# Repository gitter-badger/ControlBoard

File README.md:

ControlBoard
============

HAAG Control Board Schematics and Board Design

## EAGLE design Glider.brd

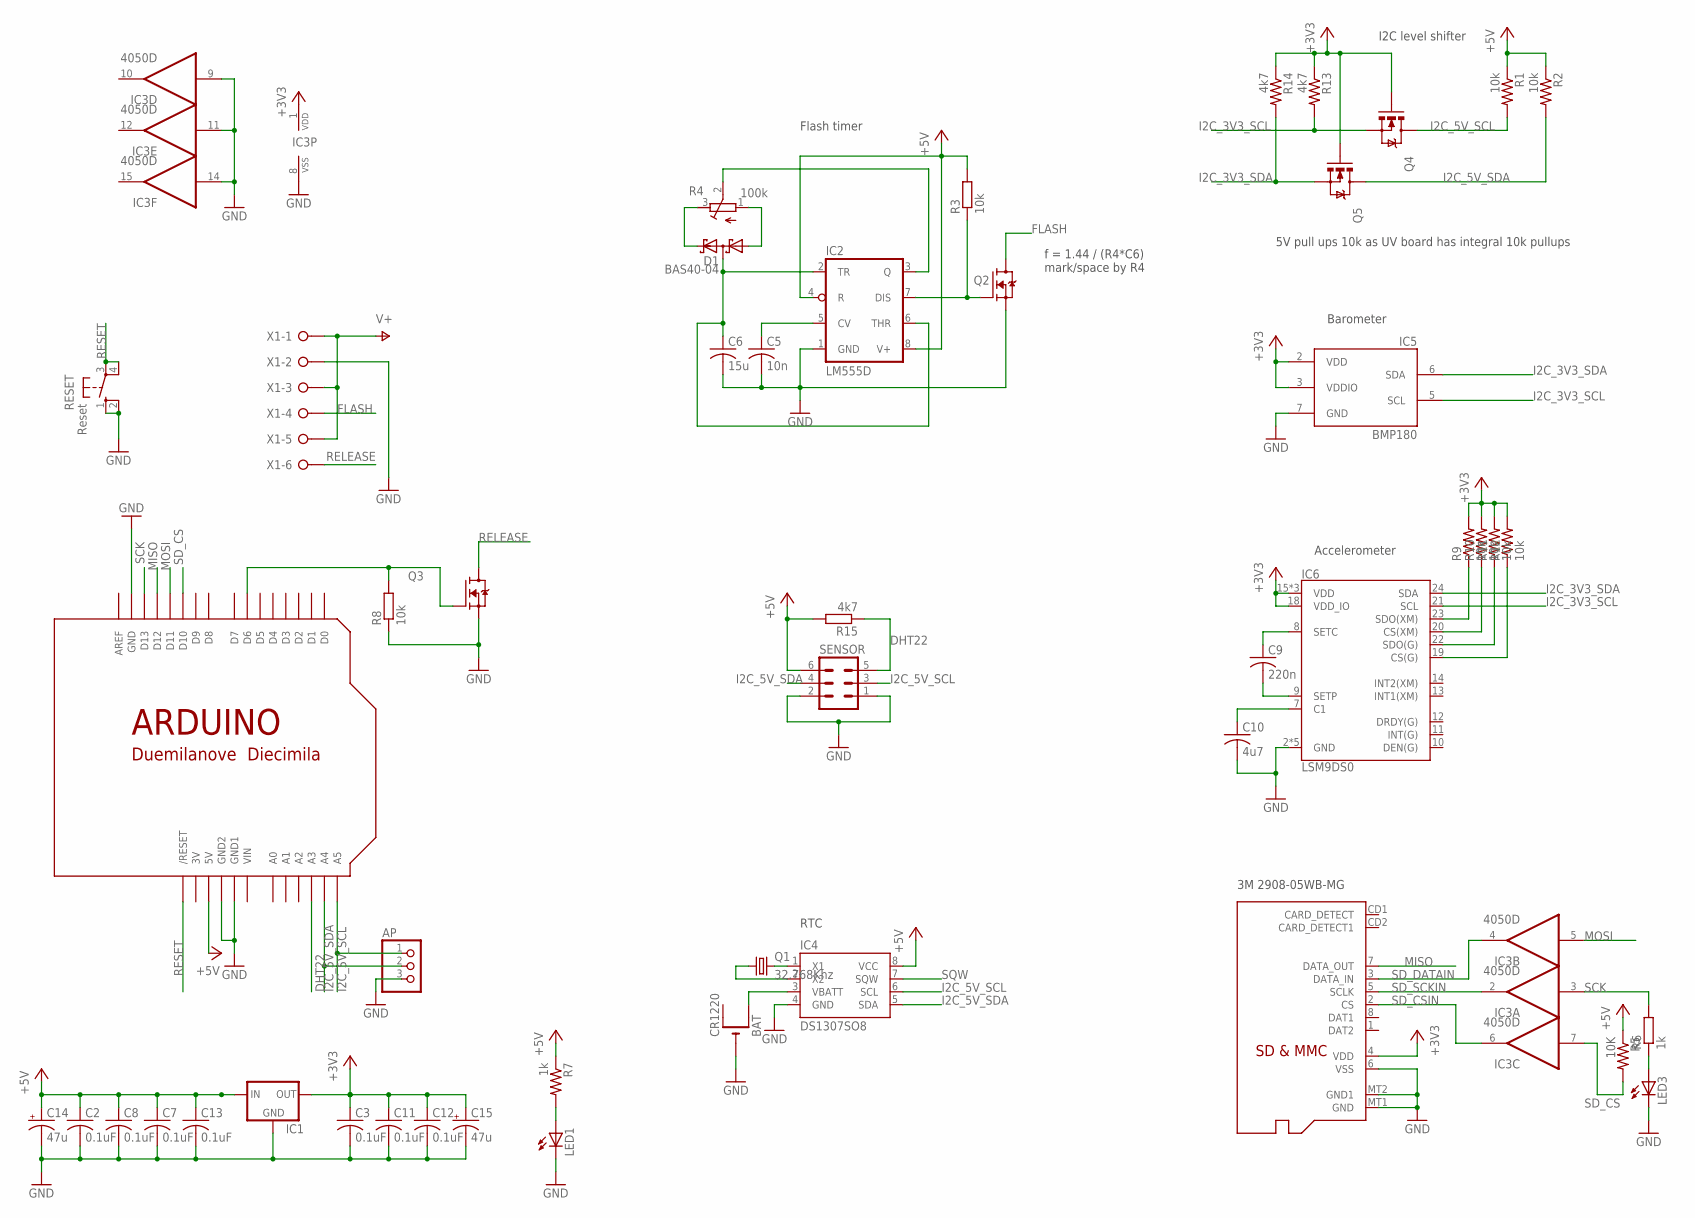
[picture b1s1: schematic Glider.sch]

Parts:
AP: PINHD-1X3; 1X03
BAT: CR1220; CR1220-THM
C2, C3, C7, C8, C11, C12, C13: 0.1uF; C0805
C5: 10n; C0805
C6: 15u; C0805
C9: 220n; C0603
C10: 4u7; C0603
C14, C15: 47u; SMC_B
D1: BAS40-04; SOT23
IC1: MCP1700TT; SOT-23
IC2: LM555D; SO08
IC3: 4050D; SO16
IC4: DS1307SO8; SO08
IC5: BMP180
IC6: LSM9DS0; LGA-24
LED1, LED3: LEDCHIPLED_0805; CHIPLED_0805
Q1: 32.768Khz; TC38H
Q2, Q3: NTD20N06LT4G; TO252
Q4, Q5: MOSFET-NCHANNELBSS123LT1G; SOT23-3
R1, R2, R3, R8, R9, R10, R11, R12: 10k; R0805
R4: 100k; RTRIM3214W
R5: 10K; R0805
R6, R7: 1k; R0805
R13, R14, R15: 4k7; R0805
RESET: Reset; B3F-10XX
SD: MICROSD
SENSOR: ML6
U$1: ARDUINODUEMILANOVE-NOHOLES; ARDUINO-NOHOLE
X1: W237-06P; W237-6P

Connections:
3V: U$1.3V
+3V3: C3.1, C11.1, C12.1, C15.+, IC1.2 (OUT), IC3.1 (VDD), IC5.2 (VDD), IC5.3 (VDDIO), IC6.15 (VDD), IC6.16 (VDD), IC6.17 (VDD), IC6.18 (VDD_IO), Q4.1 (G), Q5.1 (G), R9.2, R10.2, R11.2, R12.2, R13.1, R14.1, SD.4 (VDD)
+5V: C2.1, C7.1, C8.1, C13.1, C14.+, IC1.3 (IN), IC2.4 (R), IC2.8 (V+), IC4.8 (VCC), R1.1, R2.1, R3.2, R5.1, R7.1, R15.2, SENSOR.6, U$1.5V
DHT22: R15.1, SENSOR.5, U$1.A3
FLASH: Q2.4 (D), X1.4
GND: AP.3, BAT.-, C2.2, C3.2, C5.2, C6.2, C7.2, C8.2, C10.2, C11.2, C12.2, C13.2, C14.-, C15.-, IC1.1 (GND), IC2.1 (GND), IC3.8 (VSS), IC3.9 (I), IC3.11 (I), IC3.14 (I), IC4.4 (GND), IC5.7 (GND), IC6.2 (GND), IC6.3 (GND), IC6.4 (GND), IC6.5 (GND), IC6.6 (GND), LED1.C, LED3.C, Q2.3 (S), Q3.3 (S), R8.1, RESET.1 (S), RESET.2 (S1), SD.6 (VSS), SD.MT1 (GND), SD.MT2 (GND1), SENSOR.1, SENSOR.2, U$1.GND, U$1.GND1, U$1.GND2, X1.2
I2C_3V3_SCL: IC5.5 (SCL), IC6.21 (SCL), Q4.2 (S), R13.2
I2C_3V3_SDA: IC5.6 (SDA), IC6.24 (SDA), Q5.2 (S), R14.2
I2C_5V_SCL: AP.1, IC4.6 (SCL), Q4.3 (D), R1.2, SENSOR.3, U$1.A5
I2C_5V_SDA: AP.2, IC4.5 (SDA), Q5.3 (D), R2.2, SENSOR.4, U$1.A4
MISO: SD.7 (DATA_OUT), U$1.D12
MOSI: IC3.5 (I), U$1.D11
unnamed: BAT.+1 (+), IC4.3 (VBATT)
unnamed: IC4.1 (X1), Q1.2
unnamed: IC4.2 (X2), Q1.1
unnamed: LED3.A, R6.1
unnamed: IC2.3 (Q), R4.2 (S)
unnamed: LED1.A, R7.2
unnamed: D1.1 (A1), R4.1 (A)
unnamed: D1.2 (C2), R4.3 (E)
unnamed: C6.1, D1.3 (C1A2), IC2.2 (TR), IC2.6 (THR)
unnamed: C5.1, IC2.5 (CV)
unnamed: IC6.23 (SDO(XM)), R9.1
unnamed: IC2.7 (DIS), Q2.1 (G), R3.1
unnamed: IC6.20 (CS(XM)), R10.1
unnamed: IC6.22 (SDO(G)), R11.1
unnamed: IC6.19 (CS(G)), R12.1
unnamed: C10.1, IC6.7 (C1)
unnamed: C9.1, IC6.8 (SETC)
unnamed: C9.2, IC6.9 (SETP)
unnamed: Q3.1 (G), R8.2, U$1.D6
RELEASE: Q3.4 (D), X1.6
RESET: RESET.3, RESET.4 (P1), U$1.RESET (/RESET)
SCK: IC3.3 (I), R6.2, U$1.D13
SD_CS: IC3.7 (I), R5.2, U$1.D10
SD_CSIN: IC3.6 (O), SD.2 (CS)
SD_DATAIN: IC3.4 (O), SD.3 (DATA_IN)
SD_SCKIN: IC3.2 (O), SD.5 (SCLK)
SQW: IC4.7 (SQW)
V+: X1.1, X1.3, X1.5
VIN: U$1.VIN

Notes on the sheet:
f = 1.44 / (R4*C6) mark/space by R4
Accelerometer
I2C level shifter
5V pull ups 10k as UV board has integral 10k pullups
Barometer
3M 2908-05WB-MG
Flash timer
RTC

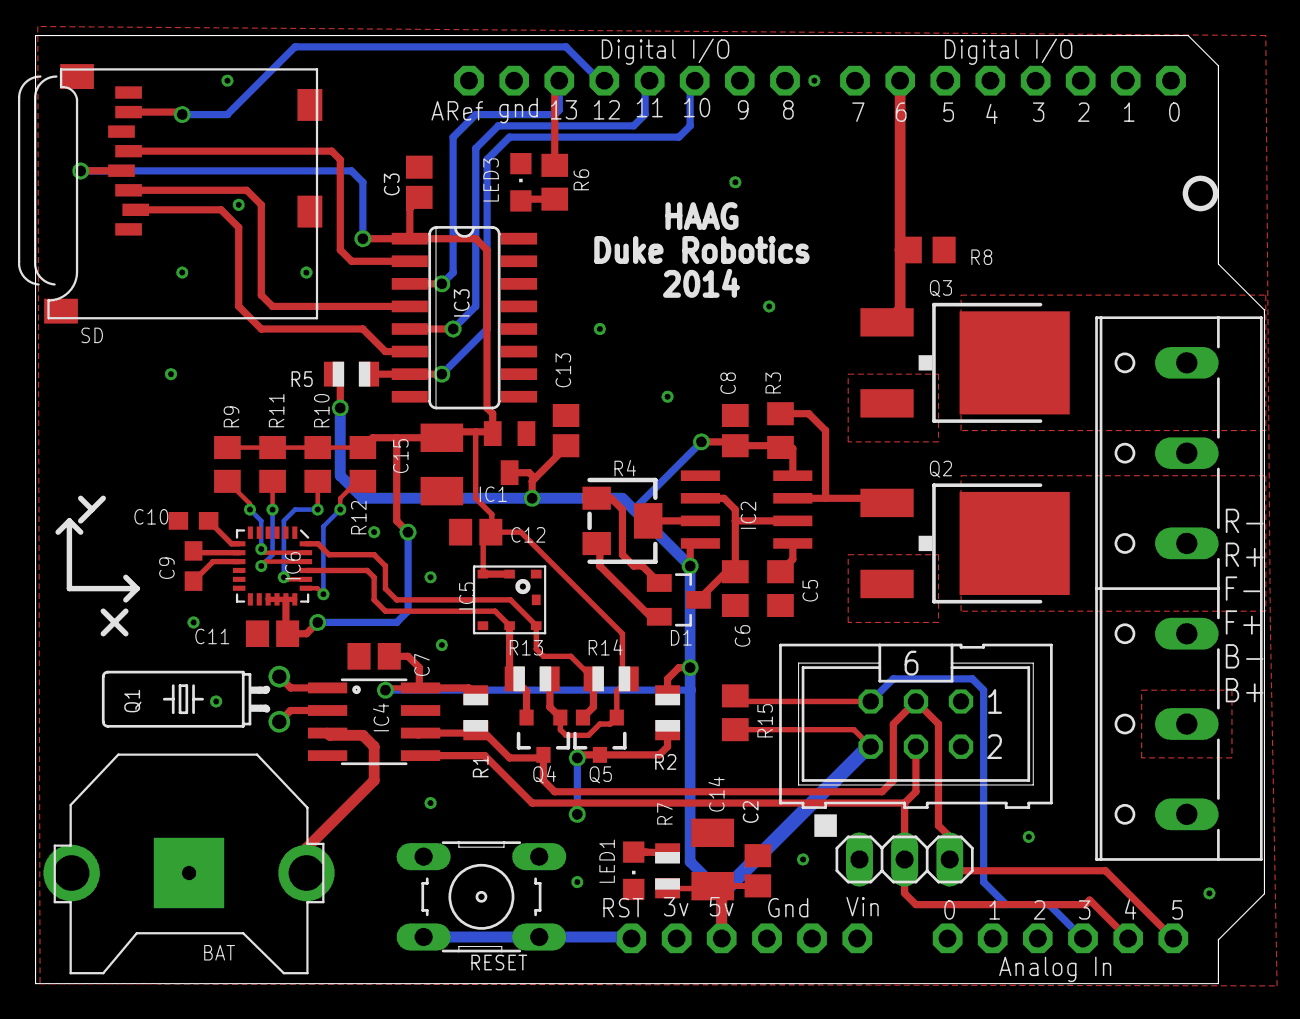
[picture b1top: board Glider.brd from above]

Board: 2 copper layers, 69.1 x 53.3 mm, 49 parts (0 on the bottom side), 38 nets.

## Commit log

2014-09-27 upload
2014-09-28 First draft of control board
2014-09-29 First draft layout - to check!
2014-09-30 Added accelerometer and barometer with associated level shifters. To be checked!
2014-10-01 Added DHT22 pullup and tidied up
2014-10-01 Didn't save...
2014-10-03 Final check, added BOM as .csv
2014-10-04 Added Gitter badge

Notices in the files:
parts and their libraries:
SparkFun-FreqCtrl: Licensing: Creative Commons ShareAlike 4.0 International - https://creativecommons.org/licenses/by-sa/4.0
